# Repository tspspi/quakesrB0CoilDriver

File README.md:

# QUAK/ESR B0 coil driver

Coil driver circuit to use full swing of 3.3V DAC to cover
range required for B0 field of electron spin resonancy
experiment driven via OPA549

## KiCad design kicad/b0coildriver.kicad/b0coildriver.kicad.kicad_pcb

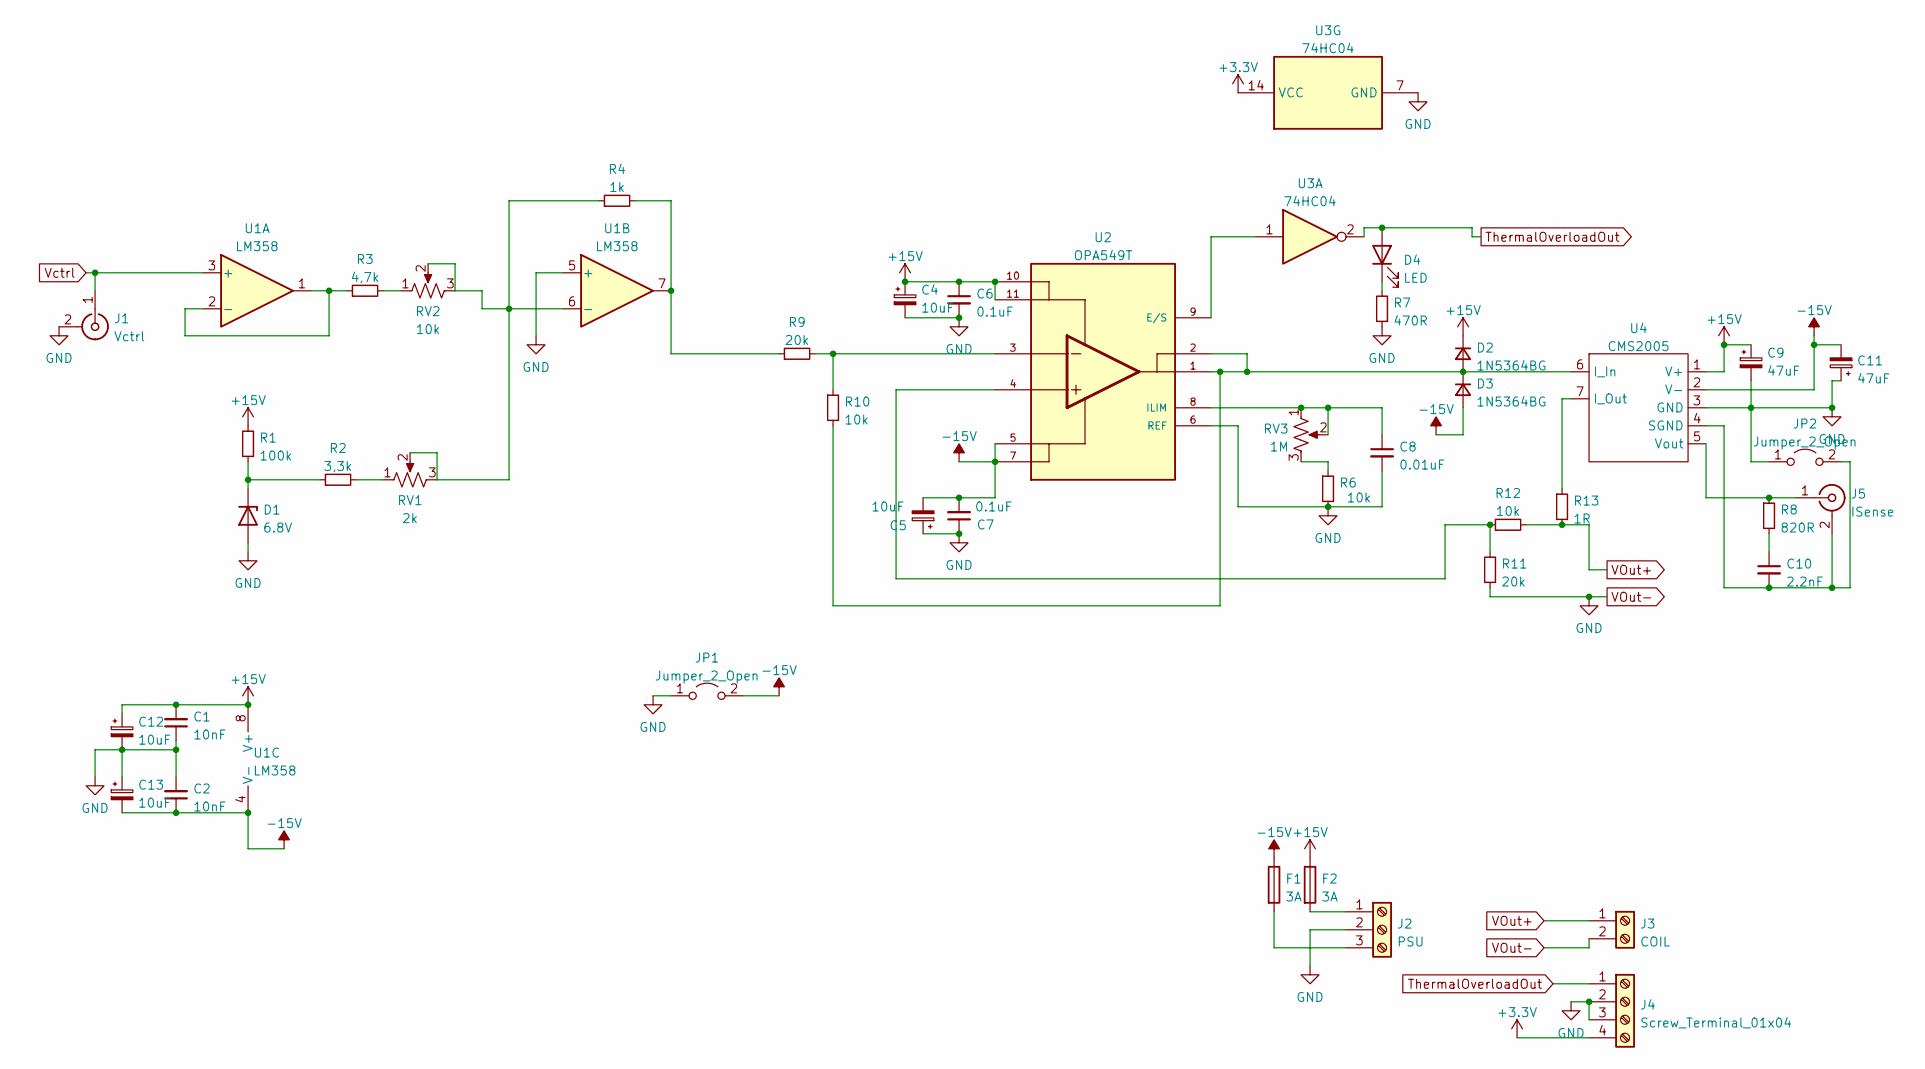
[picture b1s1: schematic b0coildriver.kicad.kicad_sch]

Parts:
C1, C2: 10nF; C_Rect_L7.0mm_W2.0mm_P5.00mm
C4, C5, C12, C13: 10uF; CP_Radial_D8.0mm_P3.80mm
C6, C7: 0.1uF; C_Rect_L7.0mm_W2.0mm_P5.00mm
C8: 0.01uF; C_Rect_L7.0mm_W2.0mm_P5.00mm
C9, C11: 47uF; CP_Radial_D8.0mm_P3.80mm
C10: 2.2nF; C_Rect_L7.0mm_W2.0mm_P5.00mm
D1: 6.8V; D_T-1_P5.08mm_Horizontal
D2, D3: 1N5364BG; D_DO-27_P15.24mm_Horizontal
D4: LED; LED_D5.0mm
F1, F2: 3A; Fuseholder_Littelfuse_100_series_5x25mm
J1: Vctrl; PinHeader_1x02_P2.54mm_Vertical
J2: PSU; PinHeader_1x03_P2.54mm_Vertical
J3: COIL; PinHeader_1x02_P2.54mm_Vertical
J4: Screw_Terminal_01x04; PinHeader_1x04_P2.54mm_Vertical
J5: ISense; PinHeader_1x02_P2.54mm_Vertical
JP1, JP2: Jumper_2_Open; PinHeader_1x02_P2.54mm_Vertical
R1: 100k; R_Axial_DIN0207_L6.3mm_D2.5mm_P10.16mm_Horizontal
R2: 3,3k; R_Axial_DIN0207_L6.3mm_D2.5mm_P10.16mm_Horizontal
R3: 4,7k; R_Axial_DIN0207_L6.3mm_D2.5mm_P10.16mm_Horizontal
R4: 1k; R_Axial_DIN0207_L6.3mm_D2.5mm_P10.16mm_Horizontal
R6, R10, R12: 10k; R_Axial_DIN0207_L6.3mm_D2.5mm_P10.16mm_Horizontal
R7: 470R; R_Axial_DIN0207_L6.3mm_D2.5mm_P10.16mm_Horizontal
R8: 820R; R_Axial_DIN0207_L6.3mm_D2.5mm_P10.16mm_Horizontal
R9, R11: 20k; R_Axial_DIN0207_L6.3mm_D2.5mm_P10.16mm_Horizontal
R13: 1R; R_Axial_DIN0207_L6.3mm_D2.5mm_P10.16mm_Horizontal
RV1: 2k; Potentiometer_Bourns_3386F_Vertical
RV2: 10k; Potentiometer_Bourns_3386F_Vertical
RV3: 1M; Potentiometer_Bourns_3386F_Vertical
U1: LM358; DIP-8_W7.62mm
U2: OPA549T; KVC; PARTREV OCTOBER 2005
U3: 74HC04; DIP-14_W7.62mm_Socket
U4: CMS2005

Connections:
+3.3V: J4.4, U3.14 (VCC)
+15V: C1.2, C4.1, C6.1, C9.1, C12.1, D2.1 (K), F2.1, R1.2, U1.8 (V+), U2.10, U2.11, U4.1 (V+)
-15V: C2.1, C5.2, C7.2, C11.2, C13.2, D3.2 (A), F1.1, JP1.2 (B), U1.4 (V-), U2.5, U2.7, U4.2 (V-)
unnamed: C8.1, RV3.1, RV3.2, U2.8 (ILIM)
unnamed: C10.1, R8.2
unnamed: C10.2, J5.2 (Ext), JP2.2 (B), U4.4 (SGND)
unnamed: D1.1 (K), R1.1, R2.1
unnamed: D2.2 (A), D3.1 (K), R10.2, U2.1, U2.2, U4.6 (I_In)
unnamed: D4.1 (K), R7.2
unnamed: F1.2, J2.3
unnamed: F2.2, J2.1
unnamed: J5.1 (In), R8.1, U4.5 (Vout)
unnamed: R2.2, RV1.1
unnamed: R3.1, U1.1, U1.2 (-)
unnamed: R3.2, RV2.1
unnamed: R4.2, R9.1, U1.7
unnamed: R9.2, R10.1, U2.3
unnamed: R11.2, R12.1, U2.4
unnamed: R13.1, U4.7 (I_Out)
unnamed: R4.1, RV1.2, RV1.3, RV2.2, RV2.3, U1.6 (-)
unnamed: R6.1, RV3.3
unnamed: U2.9 (E/S), U3.1
ThermalOverloadOut: D4.2 (A), J4.1, U3.2
VOut+: J3.1, R12.2, R13.2
VOut-: C1.1, C2.2, C4.2, C5.1, C6.2, C7.1, C8.2, C9.2, C11.1, C12.2, C13.1, D1.2 (A), J1.2 (Ext), J2.2, J3.2, J4.2, J4.3, JP1.1 (A), JP2.1 (A), R6.2, R7.1, R11.1, U1.5 (+), U2.6 (REF), U3.7 (GND), U4.3 (GND)
Vctrl: J1.1 (In), U1.3 (+)

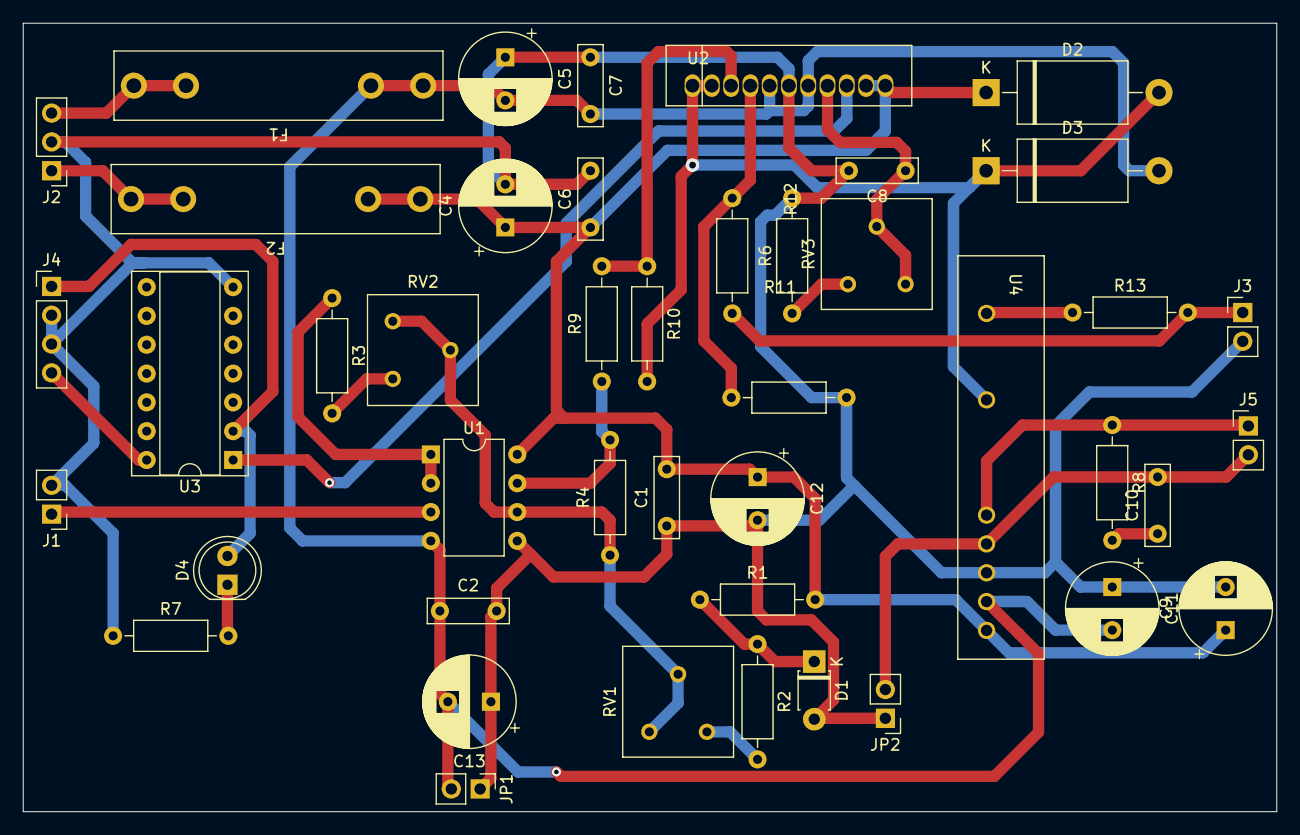
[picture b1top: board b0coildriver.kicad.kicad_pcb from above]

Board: 2 copper layers, 110.5 x 69.5 mm, 44 parts (0 on the bottom side), 26 nets.

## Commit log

2022-08-18 Added README
2022-08-19 Temperature compensating feedback network
2022-08-23 Updated board layout to new feedback network
2022-08-23 Fixed value of pullup at voltage reference
